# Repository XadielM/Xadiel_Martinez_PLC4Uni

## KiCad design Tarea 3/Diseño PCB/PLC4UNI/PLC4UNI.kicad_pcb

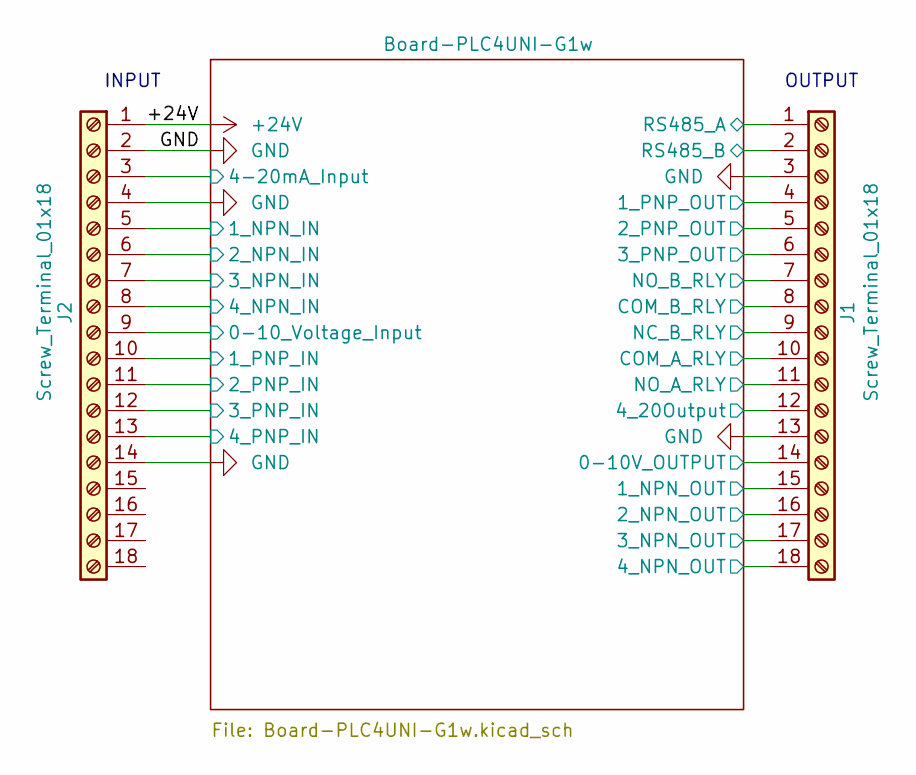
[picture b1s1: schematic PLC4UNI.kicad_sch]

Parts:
J1, J2: Screw_Terminal_01x18; TerminalBlock_MaiXu_MX126-5.0-18P_1x18_P5.00mm

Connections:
+24V: J2.1
/Board-PLC4UNI-G1w/0-10V_OUTPUT: J1.14; also elsewhere on the board
/Board-PLC4UNI-G1w/0-10_Voltage_Input: J2.9; also elsewhere on the board
/Board-PLC4UNI-G1w/1_NPN_IN: J2.5; also elsewhere on the board
/Board-PLC4UNI-G1w/1_NPN_OUT: J1.15; also elsewhere on the board
/Board-PLC4UNI-G1w/1_PNP_IN: J2.10; also elsewhere on the board
/Board-PLC4UNI-G1w/1_PNP_OUT: J1.4; also elsewhere on the board
/Board-PLC4UNI-G1w/2_NPN_IN: J2.6; also elsewhere on the board
/Board-PLC4UNI-G1w/2_NPN_OUT: J1.16; also elsewhere on the board
/Board-PLC4UNI-G1w/2_PNP_IN: J2.11; also elsewhere on the board
/Board-PLC4UNI-G1w/2_PNP_OUT: J1.5; also elsewhere on the board
/Board-PLC4UNI-G1w/3_NPN_IN: J2.7; also elsewhere on the board
/Board-PLC4UNI-G1w/3_NPN_OUT: J1.17; also elsewhere on the board
/Board-PLC4UNI-G1w/3_PNP_IN: J2.12; also elsewhere on the board
/Board-PLC4UNI-G1w/3_PNP_OUT: J1.6; also elsewhere on the board
/Board-PLC4UNI-G1w/4-20mA_Input: J2.3; also elsewhere on the board
/Board-PLC4UNI-G1w/4_20Output: J1.12; also elsewhere on the board
/Board-PLC4UNI-G1w/4_NPN_IN: J2.8; also elsewhere on the board
/Board-PLC4UNI-G1w/4_NPN_OUT: J1.18; also elsewhere on the board
/Board-PLC4UNI-G1w/4_PNP_IN: J2.13; also elsewhere on the board
/Board-PLC4UNI-G1w/COM_A_RLY: J1.10; also elsewhere on the board
/Board-PLC4UNI-G1w/COM_B_RLY: J1.8; also elsewhere on the board
/Board-PLC4UNI-G1w/NC_B_RLY: J1.9; also elsewhere on the board
/Board-PLC4UNI-G1w/NO_A_RLY: J1.11; also elsewhere on the board
/Board-PLC4UNI-G1w/NO_B_RLY: J1.7; also elsewhere on the board
/Board-PLC4UNI-G1w/RS485_A: J1.1
/Board-PLC4UNI-G1w/RS485_B: J1.2; also elsewhere on the board
GND: J1.3, J1.13, J2.2, J2.4, J2.14; also elsewhere on the board

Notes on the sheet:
OUTPUT
INPUT

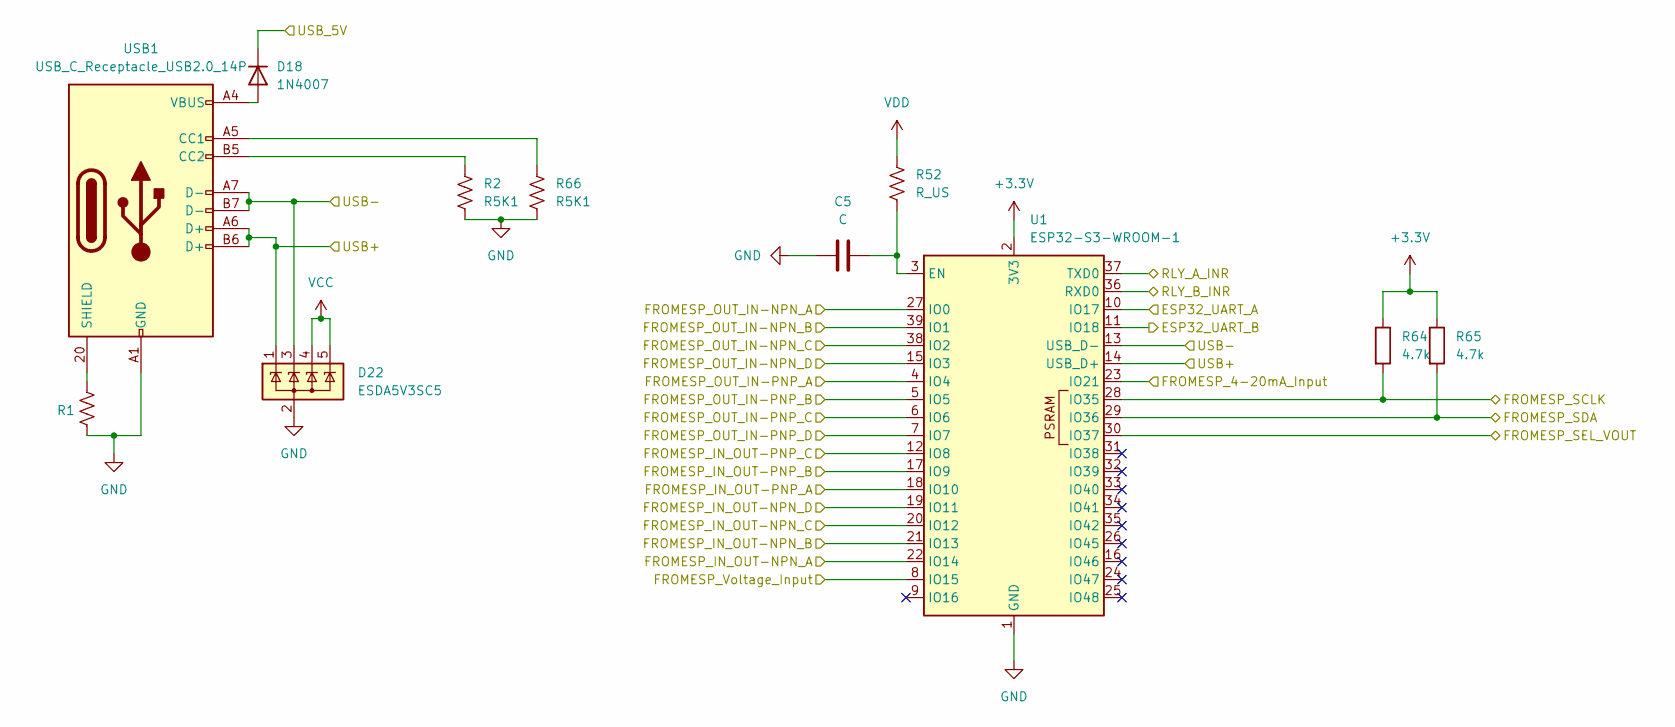
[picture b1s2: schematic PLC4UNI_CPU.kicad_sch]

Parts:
C5: C; C_1206_3216Metric_Pad1.33x1.80mm_HandSolder
D18: 1N4007; D_0603_1608Metric_Pad1.05x0.95mm_HandSolder
D22: ESDA5V3SC5; SOT-23-5
R1, R2, R66: R5K1; R_0201_0603Metric
R52: R_US; R_0201_0603Metric
R64, R65: 4.7k; R_0603_1608Metric
U1: ESP32-S3-WROOM-1
USB1: USB_C_Receptacle_USB2.0_14P; USB_C_Receptacle_HRO_TYPE-C-31-M-12

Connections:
+3.3V: R64.1, R65.1, U1.2 (3V3); also elsewhere on the board
/Board-PLC4UNI-G1w/0-10V_Output/SCLK_V: R64.2, U1.28 (IO35); also elsewhere on the board
/Board-PLC4UNI-G1w/0-10V_Output/SDA_V: R65.2, U1.29 (IO36); also elsewhere on the board
/Board-PLC4UNI-G1w/0-10V_Output/SEL: U1.30 (IO37); also elsewhere on the board
/Board-PLC4UNI-G1w/0-10_Input/Voltage_Input_toESP: U1.8 (IO15); also elsewhere on the board
/Board-PLC4UNI-G1w/4-20mA_Input/4-20mA_toESP_IN: U1.23 (IO21); also elsewhere on the board
/Board-PLC4UNI-G1w/OUT_RLY_A/RLY_A_INR: U1.37 (TXD0); also elsewhere on the board
/Board-PLC4UNI-G1w/OUT_RLY_B/RLY_B_INR: U1.36 (RXD0); also elsewhere on the board
/Board-PLC4UNI-G1w/PLC4UNI_CPU/ESP32_UART_A: U1.10 (IO17); also elsewhere on the board
/Board-PLC4UNI-G1w/PLC4UNI_CPU/ESP32_UART_B: U1.11 (IO18); also elsewhere on the board
/Board-PLC4UNI-G1w/PLC4UNI_CPU/FROMESP_IN_OUT-NPN_A: U1.22 (IO14); also elsewhere on the board
/Board-PLC4UNI-G1w/PLC4UNI_CPU/FROMESP_IN_OUT-NPN_B: U1.21 (IO13); also elsewhere on the board
/Board-PLC4UNI-G1w/PLC4UNI_CPU/FROMESP_IN_OUT-NPN_C: U1.20 (IO12); also elsewhere on the board
/Board-PLC4UNI-G1w/PLC4UNI_CPU/FROMESP_IN_OUT-NPN_D: U1.19 (IO11); also elsewhere on the board
/Board-PLC4UNI-G1w/PLC4UNI_CPU/FROMESP_IN_OUT-PNP_A: U1.18 (IO10); also elsewhere on the board
/Board-PLC4UNI-G1w/PLC4UNI_CPU/FROMESP_IN_OUT-PNP_B: U1.17 (IO9); also elsewhere on the board
/Board-PLC4UNI-G1w/PLC4UNI_CPU/FROMESP_IN_OUT-PNP_C: U1.12 (IO8); also elsewhere on the board
/Board-PLC4UNI-G1w/PLC4UNI_CPU/FROMESP_OUT_IN-NPN_A: U1.27 (IO0); also elsewhere on the board
/Board-PLC4UNI-G1w/PLC4UNI_CPU/FROMESP_OUT_IN-NPN_B: U1.39 (IO1); also elsewhere on the board
/Board-PLC4UNI-G1w/PLC4UNI_CPU/FROMESP_OUT_IN-NPN_C: U1.38 (IO2); also elsewhere on the board
/Board-PLC4UNI-G1w/PLC4UNI_CPU/FROMESP_OUT_IN-NPN_D: U1.15 (IO3); also elsewhere on the board
/Board-PLC4UNI-G1w/PLC4UNI_CPU/FROMESP_OUT_IN-PNP_A: U1.4 (IO4); also elsewhere on the board
/Board-PLC4UNI-G1w/PLC4UNI_CPU/FROMESP_OUT_IN-PNP_B: U1.5 (IO5); also elsewhere on the board
/Board-PLC4UNI-G1w/PLC4UNI_CPU/FROMESP_OUT_IN-PNP_C: U1.6 (IO6); also elsewhere on the board
/Board-PLC4UNI-G1w/PLC4UNI_CPU/FROMESP_OUT_IN-PNP_D: U1.7 (IO7); also elsewhere on the board
/Board-PLC4UNI-G1w/PLC4UNI_CPU/USB+: D22.1 (K), U1.14 (USB_D+), USB1.A6 (D+), USB1.B6 (D+)
/Board-PLC4UNI-G1w/PLC4UNI_CPU/USB-: D22.3 (K), U1.13 (USB_D-), USB1.A7 (D-), USB1.B7 (D-)
/Board-PLC4UNI-G1w/PLC4UNI_CPU/USB_5V: D18.1 (K)
GND: C5.1, D22.2 (A), R1.2, R2.2, R66.2, U1.1 (GND), U1.40 (GND), U1.41 (GND), USB1.A1 (GND), USB1.A12 (GND), USB1.B1 (GND), USB1.B12 (GND); also elsewhere on the board
unnamed: D18.2 (A), USB1.A4 (VBUS), USB1.A9 (VBUS), USB1.B4 (VBUS), USB1.B9 (VBUS)
unnamed: C5.2, R52.2, U1.3 (EN)
unnamed: R66.1, USB1.A5 (CC1)
unnamed: R2.1, USB1.B5 (CC2)
unnamed: R1.1, USB1.20 (SHIELD)
VCC: D22.4 (K), D22.5 (K); also elsewhere on the board
VDD: R52.1

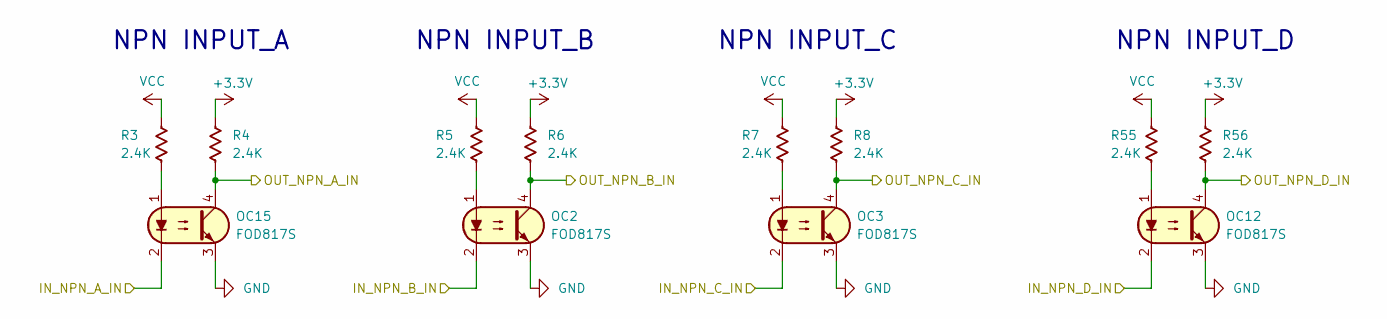
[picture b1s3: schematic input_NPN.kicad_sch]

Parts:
OC2, OC3, OC12, OC15: FOD817S; SMDIP-4_W9.53mm
R3, R4, R5, R6, R7, R8, R55, R56: 2.4K; R_0603_1608Metric

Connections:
+3.3V: R4.2, R6.2, R8.2, R56.2; also elsewhere on the board
/Board-PLC4UNI-G1w/1_NPN_IN: OC15.2; also elsewhere on the board
/Board-PLC4UNI-G1w/2_NPN_IN: OC2.2; also elsewhere on the board
/Board-PLC4UNI-G1w/3_NPN_IN: OC3.2; also elsewhere on the board
/Board-PLC4UNI-G1w/4_NPN_IN: OC12.2; also elsewhere on the board
/Board-PLC4UNI-G1w/PLC4UNI_CPU/FROMESP_OUT_IN-NPN_A: OC15.4, R4.1; also elsewhere on the board
/Board-PLC4UNI-G1w/PLC4UNI_CPU/FROMESP_OUT_IN-NPN_B: OC2.4, R6.1; also elsewhere on the board
/Board-PLC4UNI-G1w/PLC4UNI_CPU/FROMESP_OUT_IN-NPN_C: OC3.4, R8.1; also elsewhere on the board
/Board-PLC4UNI-G1w/PLC4UNI_CPU/FROMESP_OUT_IN-NPN_D: OC12.4, R56.1; also elsewhere on the board
GND: OC2.3, OC3.3, OC12.3, OC15.3; also elsewhere on the board
unnamed: OC2.1, R5.2
unnamed: OC3.1, R7.2
unnamed: OC12.1, R55.2
unnamed: OC15.1, R3.2
VCC: R3.1, R5.1, R7.1, R55.1; also elsewhere on the board

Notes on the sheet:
NPN INPUT_D
NPN INPUT_A
NPN INPUT_B
NPN INPUT_C

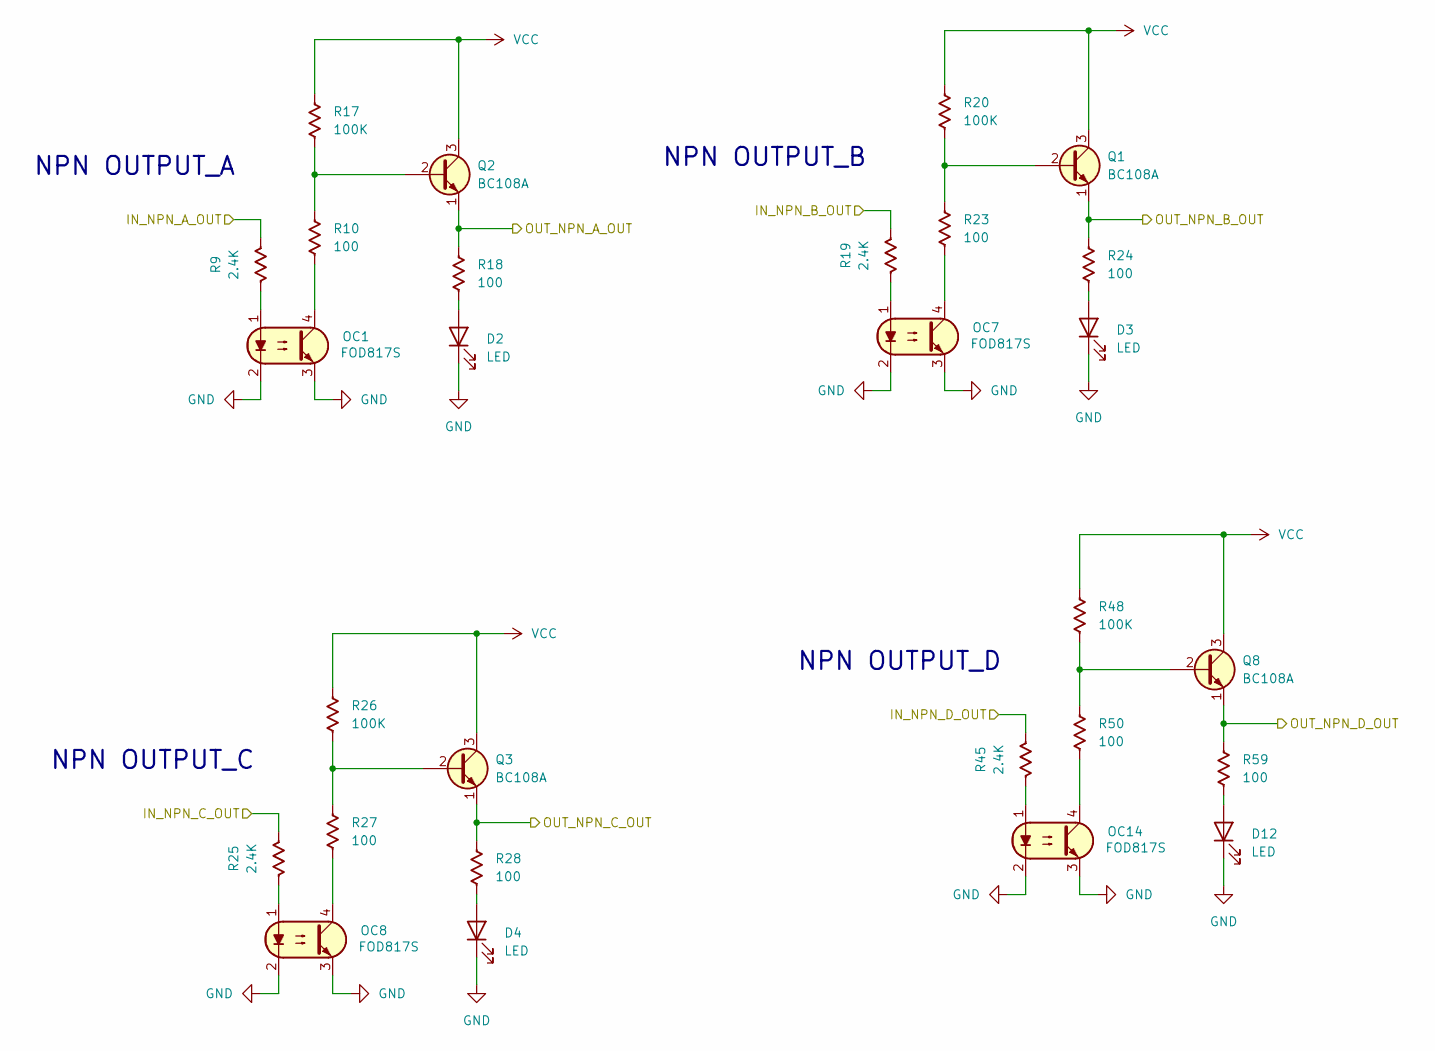
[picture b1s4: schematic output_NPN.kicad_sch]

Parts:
D2, D3, D4, D12: LED; LED_0603_1608Metric
OC1, OC7, OC8, OC14: FOD817S; SMDIP-4_W9.53mm
Q1, Q2, Q3, Q8: BC108A; TO-18-3_EBC
R9, R19, R25, R45: 2.4K; R_0603_1608Metric
R10, R18, R23, R24, R27, R28, R50, R59: 100; R_0603_1608Metric
R17, R20, R26, R48: 100K; R_0603_1608Metric

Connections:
/Board-PLC4UNI-G1w/1_NPN_OUT: Q2.1 (E), R18.2; also elsewhere on the board
/Board-PLC4UNI-G1w/2_NPN_OUT: Q1.1 (E), R24.2; also elsewhere on the board
/Board-PLC4UNI-G1w/3_NPN_OUT: Q3.1 (E), R28.2; also elsewhere on the board
/Board-PLC4UNI-G1w/4_NPN_OUT: Q8.1 (E), R59.2; also elsewhere on the board
/Board-PLC4UNI-G1w/PLC4UNI_CPU/FROMESP_IN_OUT-NPN_A: R9.1; also elsewhere on the board
/Board-PLC4UNI-G1w/PLC4UNI_CPU/FROMESP_IN_OUT-NPN_B: R19.1; also elsewhere on the board
/Board-PLC4UNI-G1w/PLC4UNI_CPU/FROMESP_IN_OUT-NPN_C: R25.1; also elsewhere on the board
/Board-PLC4UNI-G1w/PLC4UNI_CPU/FROMESP_IN_OUT-NPN_D: R45.1; also elsewhere on the board
GND: D2.1 (K), D3.1 (K), D4.1 (K), D12.1 (K), OC1.2, OC1.3, OC7.2, OC7.3, OC8.2, OC8.3, OC14.2, OC14.3; also elsewhere on the board
unnamed: D2.2 (A), R18.1
unnamed: D3.2 (A), R24.1
unnamed: D4.2 (A), R28.1
unnamed: D12.2 (A), R59.1
unnamed: OC1.1, R9.2
unnamed: OC1.4, R10.1
unnamed: OC7.1, R19.2
unnamed: OC7.4, R23.1
unnamed: OC8.1, R25.2
unnamed: OC8.4, R27.1
unnamed: OC14.1, R45.2
unnamed: OC14.4, R50.1
unnamed: Q1.2 (B), R20.1, R23.2
unnamed: Q2.2 (B), R10.2, R17.1
unnamed: Q3.2 (B), R26.1, R27.2
unnamed: Q8.2 (B), R48.1, R50.2
VCC: Q1.3 (C), Q2.3 (C), Q3.3 (C), Q8.3 (C), R17.2, R20.2, R26.2, R48.2; also elsewhere on the board

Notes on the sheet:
NPN OUTPUT_B
NPN OUTPUT_D
NPN OUTPUT_C
NPN OUTPUT_A

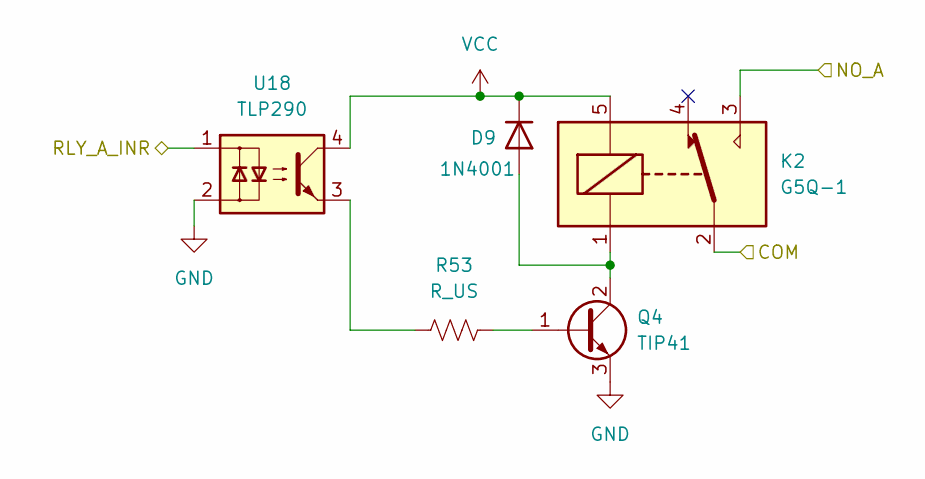
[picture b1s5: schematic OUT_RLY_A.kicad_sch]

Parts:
D9: 1N4001; D_DO-41_SOD81_P10.16mm_Horizontal
K2: G5Q-1; Relay_SPDT_Omron-G5Q-1
Q4: TIP41; TO-220-3_Vertical
R53: R_US; R_0201_0603Metric
U18: TLP290; SOP-4_4.4x2.6mm_P1.27mm

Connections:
/Board-PLC4UNI-G1w/COM_A_RLY: K2.2; also elsewhere on the board
/Board-PLC4UNI-G1w/NO_A_RLY: K2.3; also elsewhere on the board
/Board-PLC4UNI-G1w/OUT_RLY_A/RLY_A_INR: U18.1; also elsewhere on the board
GND: Q4.3 (E), U18.2; also elsewhere on the board
unnamed: D9.2 (A), K2.1, Q4.2 (C)
unnamed: Q4.1 (B), R53.2
unnamed: R53.1, U18.3
VCC: D9.1 (K), K2.5, U18.4; also elsewhere on the board

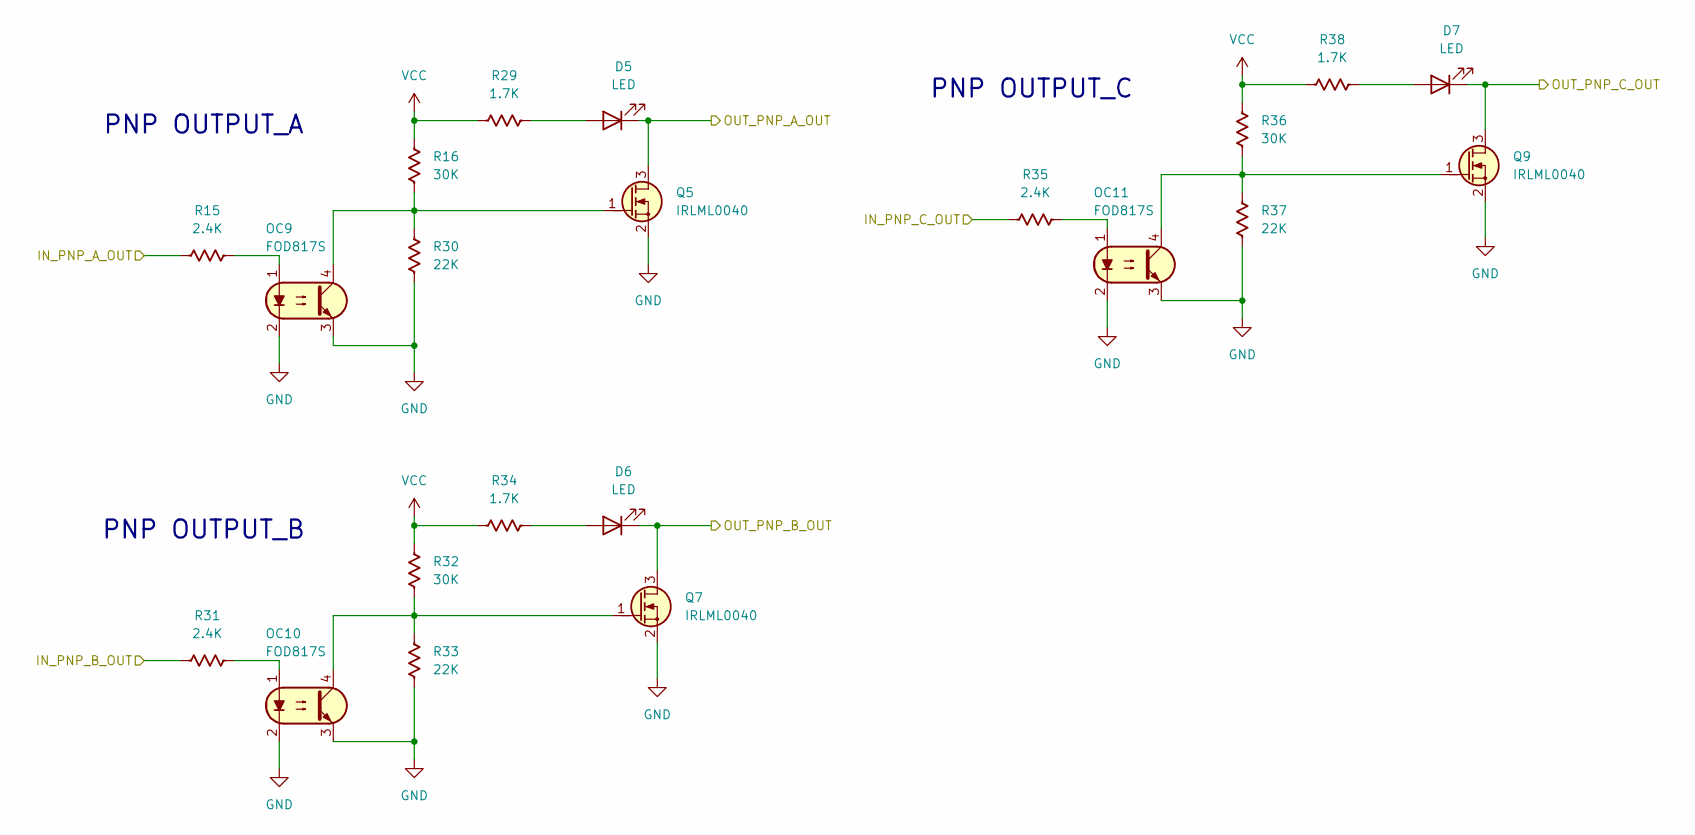
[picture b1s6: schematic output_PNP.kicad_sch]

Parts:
D5, D6, D7: LED; LED_0603_1608Metric
OC9, OC10, OC11: FOD817S; SMDIP-4_W9.53mm
Q5, Q7, Q9: IRLML0040; SOT-23
R15, R31, R35: 2.4K; R_0603_1608Metric
R16, R32, R36: 30K; R_0603_1608Metric
R29, R34, R38: 1.7K; R_0603_1608Metric
R30, R33, R37: 22K; R_0603_1608Metric

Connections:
/Board-PLC4UNI-G1w/1_PNP_OUT: D5.1 (K), Q5.3 (D); also elsewhere on the board
/Board-PLC4UNI-G1w/2_PNP_OUT: D6.1 (K), Q7.3 (D); also elsewhere on the board
/Board-PLC4UNI-G1w/3_PNP_OUT: D7.1 (K), Q9.3 (D); also elsewhere on the board
/Board-PLC4UNI-G1w/PLC4UNI_CPU/FROMESP_IN_OUT-PNP_A: R15.1; also elsewhere on the board
/Board-PLC4UNI-G1w/PLC4UNI_CPU/FROMESP_IN_OUT-PNP_B: R31.1; also elsewhere on the board
/Board-PLC4UNI-G1w/PLC4UNI_CPU/FROMESP_IN_OUT-PNP_C: R35.1; also elsewhere on the board
GND: OC9.2, OC9.3, OC10.2, OC10.3, OC11.2, OC11.3, Q5.2 (S), Q7.2 (S), Q9.2 (S), R30.1, R33.1, R37.1; also elsewhere on the board
unnamed: D5.2 (A), R29.1
unnamed: D6.2 (A), R34.1
unnamed: D7.2 (A), R38.1
unnamed: OC9.1, R15.2
unnamed: OC10.1, R31.2
unnamed: OC11.1, R35.2
unnamed: OC9.4, Q5.1 (G), R16.1, R30.2
unnamed: OC10.4, Q7.1 (G), R32.1, R33.2
unnamed: OC11.4, Q9.1 (G), R36.1, R37.2
VCC: R16.2, R29.2, R32.2, R34.2, R36.2, R38.2; also elsewhere on the board

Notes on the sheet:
PNP OUTPUT_C
PNP OUTPUT_B
PNP OUTPUT_A

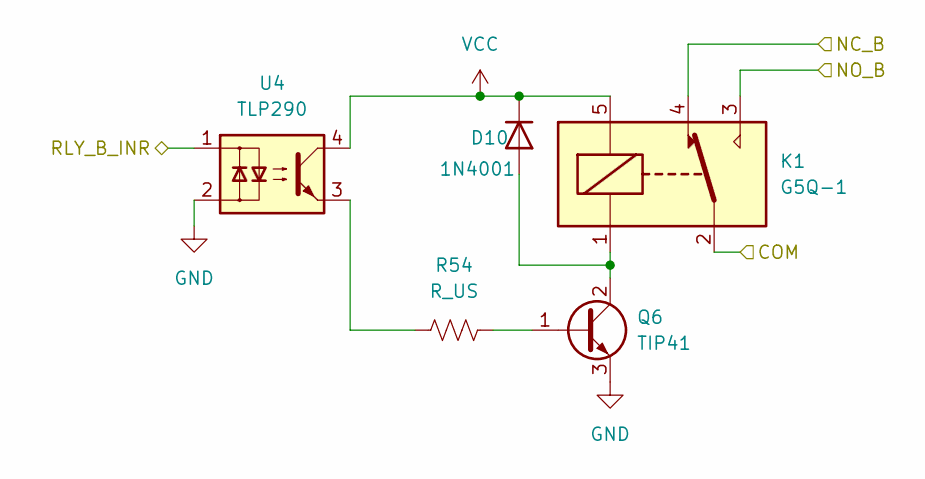
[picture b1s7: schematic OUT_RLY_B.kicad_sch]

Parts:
D10: 1N4001; D_DO-41_SOD81_P10.16mm_Horizontal
K1: G5Q-1; Relay_SPDT_Omron-G5Q-1
Q6: TIP41; TO-220-3_Vertical
R54: R_US; R_0201_0603Metric
U4: TLP290; SOP-4_4.4x2.6mm_P1.27mm

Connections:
/Board-PLC4UNI-G1w/COM_B_RLY: K1.2; also elsewhere on the board
/Board-PLC4UNI-G1w/NC_B_RLY: K1.4; also elsewhere on the board
/Board-PLC4UNI-G1w/NO_B_RLY: K1.3; also elsewhere on the board
/Board-PLC4UNI-G1w/OUT_RLY_B/RLY_B_INR: U4.1; also elsewhere on the board
GND: Q6.3 (E), U4.2; also elsewhere on the board
unnamed: D10.2 (A), K1.1, Q6.2 (C)
unnamed: Q6.1 (B), R54.2
unnamed: R54.1, U4.3
VCC: D10.1 (K), K1.5, U4.4; also elsewhere on the board

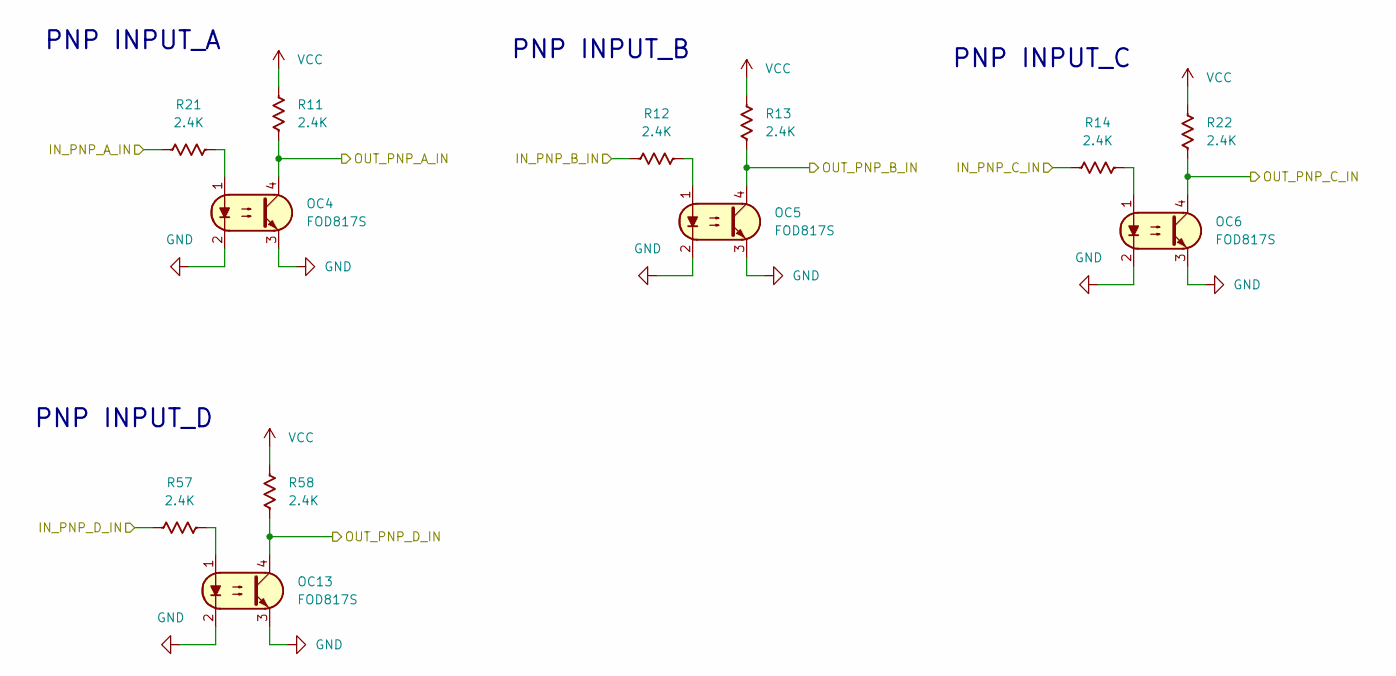
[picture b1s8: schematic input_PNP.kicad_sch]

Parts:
OC4, OC5, OC6, OC13: FOD817S; SMDIP-4_W9.53mm
R11, R12, R13, R14, R21, R22, R57: 2.4K; R_0603_1608Metric
R58: 2.4K; R_0201_0603Metric

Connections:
/Board-PLC4UNI-G1w/1_PNP_IN: R21.1; also elsewhere on the board
/Board-PLC4UNI-G1w/2_PNP_IN: R12.1; also elsewhere on the board
/Board-PLC4UNI-G1w/3_PNP_IN: R14.1; also elsewhere on the board
/Board-PLC4UNI-G1w/4_PNP_IN: R57.1; also elsewhere on the board
/Board-PLC4UNI-G1w/PLC4UNI_CPU/FROMESP_OUT_IN-PNP_A: OC4.4, R11.1; also elsewhere on the board
/Board-PLC4UNI-G1w/PLC4UNI_CPU/FROMESP_OUT_IN-PNP_B: OC5.4, R13.1; also elsewhere on the board
/Board-PLC4UNI-G1w/PLC4UNI_CPU/FROMESP_OUT_IN-PNP_C: OC6.4, R22.1; also elsewhere on the board
/Board-PLC4UNI-G1w/PLC4UNI_CPU/FROMESP_OUT_IN-PNP_D: OC13.4, R58.1; also elsewhere on the board
GND: OC4.2, OC4.3, OC5.2, OC5.3, OC6.2, OC6.3, OC13.2, OC13.3; also elsewhere on the board
unnamed: OC4.1, R21.2
unnamed: OC5.1, R12.2
unnamed: OC6.1, R14.2
unnamed: OC13.1, R57.2
VCC: R11.2, R13.2, R22.2, R58.2; also elsewhere on the board

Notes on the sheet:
PNP INPUT_B
PNP INPUT_D
PNP INPUT_A
PNP INPUT_C

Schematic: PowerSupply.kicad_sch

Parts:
C1: 100pF; C_0603_1608Metric
C2, C6: 22uF; C_0805
C3: 10uF; C_1206_3216Metric
C4: 100nF; C_0603_1608Metric
L1: 6.8uH; L_Chilisin_BMRA00040420; Part number SL0624-6R8M
R41: 196K; R_0603_1608Metric; Tolerancia 1%
R42: 62K; R_0603_1608Metric; Tolerancia 1%
U2: AP63203WU; TSOT-23-6

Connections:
+3.3V: C1.1, C2.1, C6.1, L1.1, R41.1; also elsewhere on the board
/Board-PLC4UNI-G1w/PowerSupply/USB_5V: C3.1, U2.2 (EN), U2.3 (IN)
/Board-PLC4UNI-G1w/PowerSupply/sw: C4.2, L1.2, U2.5 (SW)
GND: C2.2, C3.2, C6.2, R42.2, U2.4 (GND); also elsewhere on the board
unnamed: C4.1, U2.6 (BST)
unnamed: C1.2, R41.2, R42.1, U2.1 (FB)

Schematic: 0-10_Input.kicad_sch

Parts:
C10: 100nF; C_0603_1608Metric; Voltage 10V
D14, D15: SMAJ5.0A; D_SMA
R60: 25K; R_0603_1608Metric
R61: 10K; R_0603_1608Metric

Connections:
+3.3V: D14.1 (K); also elsewhere on the board
/Board-PLC4UNI-G1w/0-10_Input/Voltage_Input_toESP: C10.1, D14.2 (A), D15.1 (K), R60.1, R61.2; also elsewhere on the board
/Board-PLC4UNI-G1w/0-10_Voltage_Input: R60.2; also elsewhere on the board
GND: C10.2, D15.2 (A), R61.1; also elsewhere on the board

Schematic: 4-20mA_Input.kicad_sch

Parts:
C12: 100nF; C_0603_1608Metric; Voltage 10V
D13, D19: SMAJ5.0A; D_SMA
R62: 145; R_0805_2012Metric
R63: 1k; R_0603_1608Metric

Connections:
+3.3V: D19.1 (K); also elsewhere on the board
/Board-PLC4UNI-G1w/4-20mA_Input: R62.1, R63.1; also elsewhere on the board
/Board-PLC4UNI-G1w/4-20mA_Input/4-20mA_toESP_IN: C12.1, D13.1 (K), D19.2 (A), R63.2; also elsewhere on the board
GND: C12.2, D13.2 (A), R62.2; also elsewhere on the board

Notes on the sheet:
Entrada 4-20mA

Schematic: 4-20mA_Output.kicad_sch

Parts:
C13: 220pF; C_0603_1608Metric
C14: 1uF; C_0603_1608Metric
C15: 0.1uF; C_0603_1608Metric
D17: BZT52C12_C2891780; D_SOD-123; LCSC Part C2891780
D20: SMAJ33A; D_SMA
D21: MRA4007T3G; D_SMA
Q10: IRLML6402TRPBF-JSM; SOT-23; LCSC Part C18190991
R43, R46: 4.7K; R_0603_1608Metric
R47: 100K; R_0603_1608Metric
R49: 15; R_0805_2012Metric
R51: 2.5K; R_0603_1608Metric
U3: GP8303-TC50-EW; SSOP-10_3.9x4.9mm_P1.00mm

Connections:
+3.3V: R43.1, R46.1; also elsewhere on the board
/Board-PLC4UNI-G1w/0-10V_Output/SCLK_V: R46.2, U3.1 (SLCK); also elsewhere on the board
/Board-PLC4UNI-G1w/0-10V_Output/SDA_V: R43.2, U3.2 (SDA); also elsewhere on the board
/Board-PLC4UNI-G1w/4_20Output: D21.1 (K); also elsewhere on the board
GND: C13.2, C14.2, C15.2, D20.2 (A2), R47.2, R51.2, U3.6 (GND); also elsewhere on the board
unnamed: C14.1, D17.2 (A), Q10.1 (G), R47.1
unnamed: C15.1, D20.1 (A1), Q10.3 (D), R49.1
unnamed: D21.2 (A), R49.2
unnamed: Q10.2 (S), U3.8 (IOUT)
unnamed: C13.1, R51.1, U3.7 (SET)
VCC: D17.1 (K), U3.5 (VCC); also elsewhere on the board

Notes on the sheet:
Salida 4-20mA

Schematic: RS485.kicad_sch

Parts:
J4: Conn_01x03; PinHeader_1x03_P2.54mm_Vertical
U21: SOIC127P600X175-8N

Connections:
+3.3V: U21.1 (VCC); also elsewhere on the board
/Board-PLC4UNI-G1w/PLC4UNI_CPU/ESP32_UART_A: U21.4 (´RX); also elsewhere on the board
/Board-PLC4UNI-G1w/PLC4UNI_CPU/ESP32_UART_B: U21.3 (TX); also elsewhere on the board
/Board-PLC4UNI-G1w/RS485_B: J4.8 (Pin_1), U21.8 (B); also elsewhere on the board
GND: U21.2 (GND); also elsewhere on the board

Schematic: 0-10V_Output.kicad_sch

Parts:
C8: 100nF; C_0805_2012Metric
C9: 1uF; C_0805_2012Metric_Pad1.18x1.45mm_HandSolder
D11: SMF24A; D_SMF; LCSC# C7495269
R44: 10k; R_0603_1608Metric
U19: SOIC-8_5.3x5.3mm_P1.27mm

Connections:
/Board-PLC4UNI-G1w/0-10V_OUTPUT: C8.2, D11.1 (A1), U19.6 (VOUT); also elsewhere on the board
/Board-PLC4UNI-G1w/0-10V_Output/SCLK_V: U19.1 (SCLK); also elsewhere on the board
/Board-PLC4UNI-G1w/0-10V_Output/SDA_V: U19.2 (SDA); also elsewhere on the board
/Board-PLC4UNI-G1w/0-10V_Output/SEL: R44.1, U19.7 (SEL); also elsewhere on the board
GND: C8.1, C9.1, D11.2 (A2), U19.5 (GND); also elsewhere on the board
unnamed: C9.2, R44.2, U19.8 (V5V)
VCC: U19.4 (VCC); also elsewhere on the board

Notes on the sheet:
Salida 0-10V

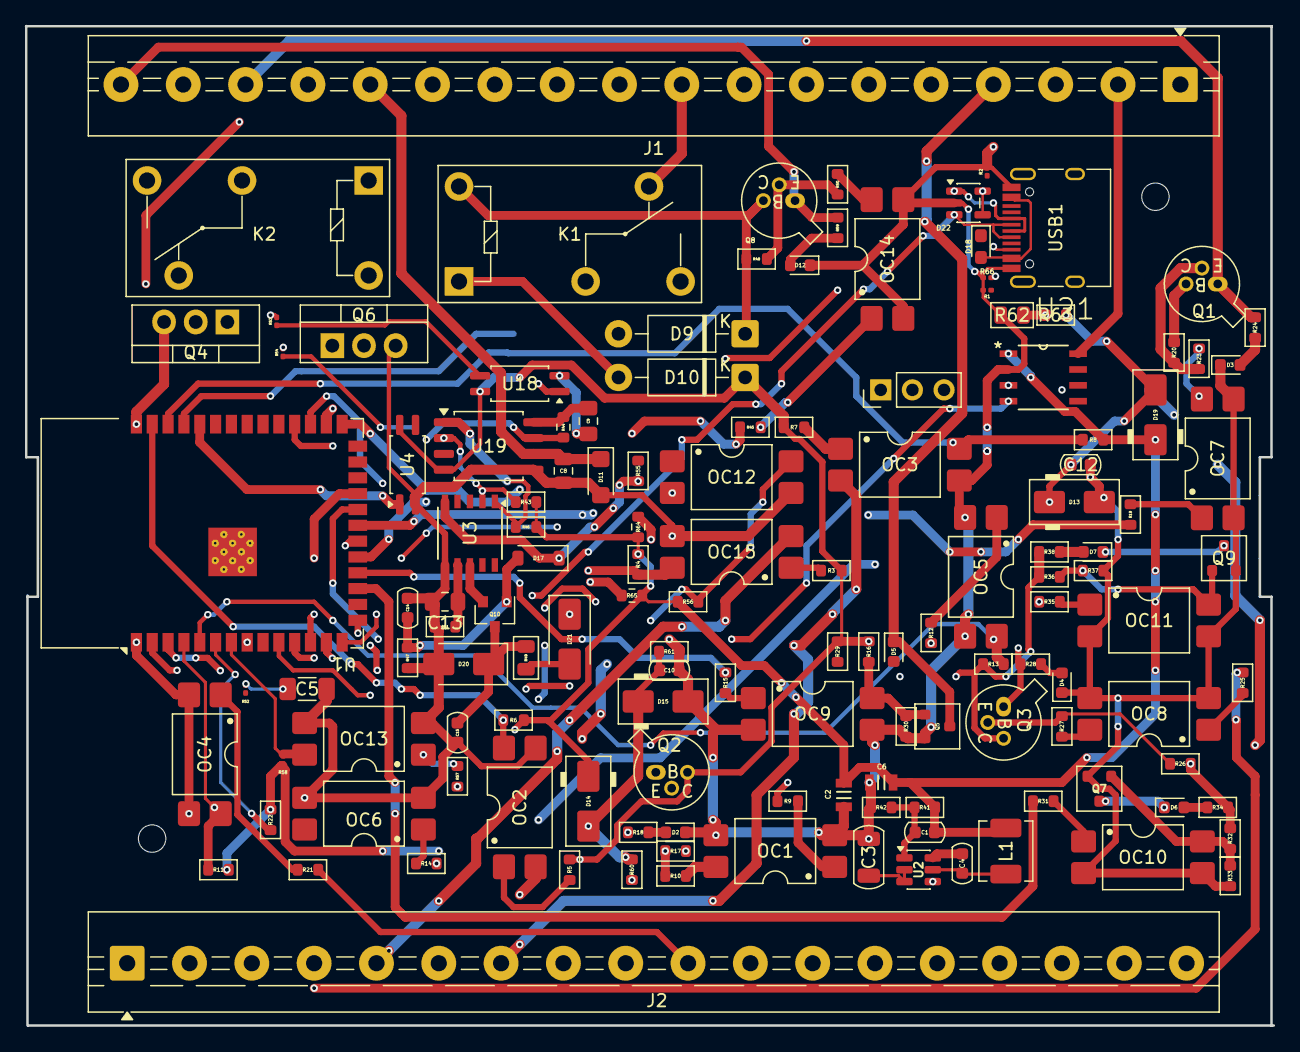
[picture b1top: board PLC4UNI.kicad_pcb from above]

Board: 4 copper layers, 100.1 x 80.2 mm, 135 parts (0 on the bottom side), 107 nets.

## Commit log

2025-09-18 Creando repositorio
2025-09-18 Documento del proyecto revision 1
2025-09-18 Subiendo archivo del proyecto
2025-09-18 Archivo del proyecto
    Convirtiendolo a PDF
2025-09-18 Convirtiendo archivo en PDF
2025-09-18 Convirtiendo archivo a PDF Rev1
2025-09-26 Diseño del case en SolidEdge
2025-09-26 Diseño del plastic case
2025-10-03 Diseño plastic case
2025-10-08 Diseño PCB KiCad
2025-10-08 Plantilla del proyecto
2025-10-10 Tarea 1
2025-10-10 Tarea 2
2025-10-10 Tarea 3
2025-10-10 Investigacion de esquematico
2025-11-26 Tarea 3
2025-12-05 tarea 3 - update
2025-12-08 Tarea - Update
2025-12-10 Tarea 4
2025-12-12 Tarea 5 - Update
2025-12-12 Tarea 4 - Update
2025-12-12 Tarea 6
